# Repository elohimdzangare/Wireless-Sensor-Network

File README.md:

# ESP32 Wireless Sensor Network

A wireless environmental monitoring system using battery powered ESP32 sensor nodes that measure temperature, humidity and light across three locations. A central gateway collects everything and sends it to MATLAB for live plotting and logging.

**Status:** Core system is built and working end to end (nodes to gateway to MATLAB). All three nodes and the gateway have since been redesigned as custom PCBs. Not currently running further test sessions, though one more test run may happen in the future.

---

## Overview

Three sensor nodes (Room A, B, C) each have a DHT22 and a BH1750 sensor and run off 4x AA batteries. Each node wakes up from deep sleep, takes a reading, sends it to the gateway over ESP-NOW, tells the gateway how long it's about to sleep for, then powers down again. The gateway stays on all the time, keeps track of all three nodes, manages 8 status LEDs, and forwards everything to MATLAB over TCP so it can be logged and plotted live.

Rooms are just labelled A, B and C for now instead of actual room names, so the sensors can be moved around without having to change any code. A separate note of what each letter actually corresponds to is kept somewhere.

---

## Possible Applications

- **Greenhouse or shed monitoring**: battery powered nodes with long sleep intervals make sense for outbuildings that don't have easy power access, where you still want to know conditions without running cables.
- **Home climate monitoring**: tracking temperature, humidity and light across different rooms to spot patterns, like which rooms run cold in winter or get too much direct sun, without needing a smart home hub.
- **Damp/mould risk detection**: persistently high humidity in an enclosed space like a basement is an early warning sign for mould risk, this system could flag rooms worth checking on.

---

## Repo Structure

```
/sensor-network
├── README.md
├── sensor_log.txt
├── /gateway
│   └── gateway_matlab.ino       (final gateway sketch)
├── /node
│   └── sensor_node_final.ino    (final sensor node sketch, used on all 3 nodes)
├── /matlab
│   └── src.m
└── /archive                     (earlier test sketches, kept for reference)
    ├── sensor_test.ino
    ├── sensor_node_test.ino
    ├── gateway_receive_test.ino
    ├── gateway_receive_final.ino
    └── hotspot_connection_test.ino
└── /images                     (images of the network)
    ├── Full Network.jpg
    ├── Gateway 3D Render.png
    ├── Gateway PCB Layout.png
    ├── Gateway.jpg 
    ├── Node 3D Render.png
    ├── Node PCB Layout.png 
    ├── Sensor Nodes.jpg
    ├── gateway_schematic.png
    ├── node_schematic.png
    └── updated node schematic.png
```

The `/archive` folder is just earlier versions and one-off test sketches from along the way (testing the sensors before adding ESP-NOW, testing the gateway before connecting it to MATLAB, etc). Not needed to actually run the project, just there to show how it was built up step by step.

---

## Hardware

| Component | Quantity | Notes |
|-----------|----------|-------|
| ESP32 (regular size) | 4 | 3 sensor nodes + 1 gateway |
| DHT22 (AZDelivery) | 3 | Temperature and humidity, one per node |
| BH1750FVI (ARCELI) | 3 | Light level in lux, one per node |
| 4x AA batteries | 3 sets | One set per sensor node, into VIN |
| LEDs | 8 | All status LEDs are on the gateway |
| Resistors | 8 | 470Ω, used for all LEDs regardless of colour |

> **Sensor power:** both sensors on every node need their VCC wired to the ESP32's 3.3V pin, not VIN. VIN is unregulated, so it just passes whatever voltage is feeding it straight through. Wiring a sensor to VIN instead of 3.3V caused issues, more on that in the Debugging section below.

> **Gateway power:** currently running off USB during testing (power bank or laptop). The 5V pin from USB powers the LED circuit. All ESP32 ground pins are tied to a shared ground.

---

## Network Architecture

```
[Node: Room A]  DHT22 + BH1750  ──┐
[Node: Room B]  DHT22 + BH1750  ──┼──(ESP-NOW)──> [Gateway ESP32] ──(TCP, port 8080)──> [MATLAB]
[Node: Room C]  DHT22 + BH1750  ──┘
   4x AA, deep sleep                              connected to WiFi, always on
```

- **Nodes to gateway:** ESP-NOW. Deep sleep wipes the chip's RAM every time it wakes up, so reconnecting to WiFi from scratch each cycle would take 1 to 3 seconds and use a lot of current for a battery powered node. ESP-NOW skips all that, the node just re-registers the gateway as a peer and sends straight away, no router needed.
- **Gateway to MATLAB:** TCP over WiFi. Only the gateway needs an actual WiFi connection since it's the only one that's always awake, so it only pays that startup cost once.
- **WiFi channel:** ESP-NOW and the gateway's WiFi connection use the same radio, so they need to be on the same channel. The nodes default to channel 1 since they never actually connect to WiFi. So far the gateway has landed on channel 1 both times it connected, once to a phone hotspot and once to home WiFi, so this hasn't been an issue yet. If it ever lands on a different channel, ESP-NOW between the nodes and gateway would stop working without much warning.

---

## Sensor Node Behaviour

Every wake cycle goes through `setup()` from scratch, since deep sleep wipes RAM and there's no way to "resume" where you left off:

1. Wake up from deep sleep (timer based)
2. Set up sensors, with a short delay to let them stabilise
3. Set up WiFi station mode and ESP-NOW, re-register the gateway as a peer
4. Read the DHT22 and BH1750
5. Build a `MSG_DATA` packet and send it to the gateway, including flags for whether each sensor read worked
6. Send a `MSG_SLEEP` packet saying how long it's about to sleep for
7. Set the wake up timer and go into deep sleep

Each node currently sleeps for **360 seconds (6 minutes)**, which works out to 10 readings an hour. Each node tells the gateway its own sleep duration in the sleep message, so if you ever want to change one node's interval you don't need to touch the gateway code at all.

> **Sensor settling time:** right after waking up, the sensors need a moment before their first reading can be trusted, especially the DHT22 which often fails its very first read after power up. The node code adds about a 2 second delay before reading, and retries the DHT22 once if the first attempt comes back invalid.

### Data Packet Structure

```cpp
typedef struct {
  uint8_t  node_id;             // 1 = Room A, 2 = Room B, 3 = Room C
  uint8_t  msg_type;            // 0 = MSG_DATA, 1 = MSG_SLEEP
  float    temperature;         // in °C, -999 if DHT22 failed
  float    humidity;            // in %, -999 if DHT22 failed
  float    lux;                 // -999 if BH1750 failed
  bool     dht_ok;
  bool     bh1750_ok;
  uint32_t sleep_duration_sec;  // only matters when msg_type == MSG_SLEEP
} SensorPacket;
```

A node always sends a data packet every cycle, even if a sensor failed. The idea is that whether a node can be reached and whether its sensors are actually working should be tracked separately, so a broken sensor doesn't make the whole node look offline. If a reading fails it just gets sent as -999 with the matching `_ok` flag set to false.

---

## Gateway Behaviour

- Runs a boot sequence with all the LEDs as a quick self test, then connects to WiFi and starts a TCP server on port 8080
- Stays on all the time, accepts a MATLAB connection whenever one comes in
- Handles incoming ESP-NOW packets based on `msg_type`:
  - `MSG_SLEEP` works out when that node should next wake up (current time plus the sleep duration it gave plus a grace window) and turns that node's awake LED off
  - `MSG_DATA` flashes the RX LED, turns the awake LED back on, updates whether that node has a sensor fault, clears any "unreachable" flag, and forwards the data to MATLAB
- Keeps checking if any sleeping node has gone past its expected wake up time, and flags it as unreachable if so
- Sends `STATUS:`, `ERROR:` and `DATA:` messages to Serial and to MATLAB at the same time
- Flashes the TX LED every time something gets sent to MATLAB

---

## Gateway LEDs

| LED | Colour | What it does |
|-----|--------|---------------|
| Room A RX | Blue | Flashes for 100ms when a packet comes in from Room A |
| Room A Awake/Asleep | White | On while Room A is awake, off once it announces it's sleeping |
| Room B RX | Orange | Flashes for 100ms when a packet comes in from Room B |
| Room B Awake/Asleep | White | On while Room B is awake, off once it announces it's sleeping |
| Room C RX | Yellow | Flashes for 100ms when a packet comes in from Room C |
| Room C Awake/Asleep | White | On while Room C is awake, off once it announces it's sleeping |
| Data Sent (TX to MATLAB) | Green | Flashes for 100ms whenever a message goes out to MATLAB |
| Error | Red | See the error states below |

All the LED flashing is non-blocking. The usual way to blink an LED is `digitalWrite(HIGH)`, then `delay(100)`, then `digitalWrite(LOW)`, but `delay()` freezes the whole chip for that time, including the part that listens for incoming ESP-NOW packets. So instead, the gateway just remembers what time an LED turned on, and checks on every loop whether 100ms has passed yet to turn it back off. Same blink, but the gateway never actually stops and can't miss a packet while waiting.

### Error LED States

| State | Behaviour | What it means |
|-------|-----------|----------------|
| `ERROR_NONE` | Off | Everything's fine |
| `ERROR_SENSOR_FAULT` | Slow blink, 500ms on/off | A node is still reachable but one of its sensors failed |
| `ERROR_NODE_UNREACHABLE` | Solid on | A node didn't wake up in time, missed its expected window |

If both are happening at once, unreachable wins and the LED goes solid. The reason behind this is that a node going completely silent is worse than one sensor on one node acting up.

### Gateway Pin Assignments

| Define | GPIO | LED |
|--------|------|-----|
| `A_RX` | 27 | Room A Receive |
| `A_AWAKE` | 14 | Room A Awake |
| `B_RX` | 32 | Room B Receive |
| `B_AWAKE` | 33 | Room B Awake |
| `C_RX` | 4 | Room C Receive |
| `C_AWAKE` | 16 | Room C Awake |
| `HUB_ERROR` | 22 | Error |
| `HUB_RECEIVE` | 19 | Data Sent / TX to MATLAB |

### Node Pin Assignments (same on all 3 nodes)

| Function | GPIO |
|----------|------|
| BH1750 SDA | 26 |
| BH1750 SCL | 27 |
| DHT22 Data | 25 |

### Boot Sequence

When the gateway powers on, it runs through a little self test before doing anything else: every LED pin gets forced LOW first (some GPIO pins can come up HIGH for a moment on boot before any code runs, so this clears that out), then each LED lights up one at a time, then all 8 flash together twice, then everything turns off and normal operation starts.

### LED Resistors

| Colour | Forward Voltage |
|--------|------------------|
| Red | 2.0-2.2V |
| Blue | 3.0-3.2V |
| White | 3.0-3.2V |
| Yellow | 1.8-2.0V |
| Green | 3.0-3.2V |
| Orange | 1.8-2.0V |

All LEDs are rated for 20mA forward current. A single 470Ω resistor value was used for every LED regardless of colour, just for simplicity. This means they're not all running at the same brightness or current, but it's not really an issue since these are just status indicators and don't need to be especially bright.

---

## Message Protocol

All messages are sent line by line from the gateway, to both Serial and to MATLAB over TCP at the same time.

```
STATUS:GATEWAY_READY
STATUS:ROOMA_SLEEPING:duration=360
STATUS:ROOMA_RECONNECTED
ERROR:ROOMB_TIMEOUT
ERROR:ROOMC_DHT_FAILURE
ERROR:ROOMC_BH1750_FAILURE
DATA:ROOMA:24.50,68.90,73.33
```

- `DATA:<ROOM>:<temperature>,<humidity>,<lux>`, one line per node per reading
- `STATUS:<ROOM>_SLEEPING:duration=<seconds>`, sent right before a node powers down
- `STATUS:<ROOM>_RECONNECTED`, sent if a node that had been flagged unreachable sends data again
- `ERROR:<ROOM>_TIMEOUT`, a node missed its expected wake up window
- `ERROR:<ROOM>_DHT_FAILURE` / `ERROR:<ROOM>_BH1750_FAILURE`, sent alongside the data line when a sensor on an otherwise working node fails

---

## Timeout / Error Logic

A fixed timeout doesn't really work once nodes are sleeping for minutes at a time, it would keep falsely triggering during completely normal sleep. So instead:

- When a sleep message comes in, the gateway works out `expected_wake_time = millis() + (sleep_duration_sec * 1000) + GRACE_WINDOW_MS`
- `ERROR:ROOMX_TIMEOUT` only fires if that node hasn't sent a data packet by its own `expected_wake_time`
- Any data packet clears the unreachable flag and resets the expected wake time back to 0 until the next sleep message
- If a node comes back after being flagged unreachable, the gateway sends `STATUS:ROOMX_RECONNECTED`

**Current values:**
- Sleep interval: 360 seconds (6 minutes), 10 readings an hour
- Grace window: 25 seconds, picked to comfortably cover a typical wake up to send cycle (roughly 2-3 seconds: booting, sensor settling, reconnecting WiFi/ESP-NOW, reading, sending) with some buffer for slower cycles, while still being small compared to the 6 minute interval

---

## MATLAB Responsibilities

- Connects to the gateway with `tcpclient(GATEWAY_IP, 8080)`
- Reads incoming lines and checks the prefix:
  - `STATUS:` gets printed to console with a timestamp and written to the log file
  - `ERROR:` gets printed to console (in red, via stderr) and written to the log file
  - `DATA:` gets parsed into temperature/humidity/lux per room and the live plots get updated
- Logs every `STATUS`/`ERROR` message into `sensor_log.txt`, which keeps appending across sessions
- Plots live data in 3 stacked subplots (temperature, humidity, light), each one showing all 3 rooms as separate lines, with a rolling window of recent points

> The gateway's IP address can change depending on whatever network it joins, since it's assigned by DHCP. The Serial Monitor must be checked each session and update the IP in the MATLAB script if needed.

---

## Debugging / Errors Encountered

A running list of the actual problems hit while building this, since most of them weren't obvious from the code alone.

**LED wouldn't light up no matter what**
Spent ages checking polarity, resistor values, GPIO pin mapping, even swapped pins entirely. Eventually traced it to the breadboard itself. The long breadboard I had purchased had a physical gap splitting the ground rail into two separate halves that aren't actually connected to each other. The ESP32's ground was in one half and the LED circuit's ground was in the other half, so they were never connected despite looking like the same rail. Fixed by bridging both halves with a jumper wire.

**BH1750 "device not configured" error, but only sometimes**
The BH1750 worked fine on a direct 6V supply but kept failing with this error once running off USB. Turned out both sensors had their VCC wired to VIN instead of 3.3V. VIN is unregulated so it just passes through whatever is feeding it, meaning the BH1750 (rated for 2.4 to 3.6V) was actually running at close to 5 or 6V depending on the power source. It happened to behave at 6V but not at 5V from USB, which made it look inconsistent rather than just wrong. Moving both sensors' VCC to the 3.3V pin fixed it completely. This also matters for the battery powered nodes specifically, since a sensor wired to VIN would get less reliable as the battery drains.

**GPIO14 turning on by itself before any code ran**
Powered on the gateway and noticed one LED was already lit before any sketch had even done anything. Some ESP32 GPIO pins default to a HIGH state for a moment during boot, before `setup()` runs. Fixed by forcing every LED pin LOW right at the very start of the boot sequence function.

**Error LED stuck blinking even while a node was asleep**
After adding deep sleep, the gateway kept showing a sensor fault for a node that was just sleeping normally. This was because the gateway didn't yet know how to tell apart a sleep announcement from a regular data packet, so the last reading it saw before the node went quiet (which happened to have a sensor fault from sensors not being settled yet) just stayed stuck. Fixed by adding sensor settling delays on the node side, and by having the gateway properly handle `MSG_SLEEP` messages separately from `MSG_DATA`.

---

## Future Features (Not Built Yet)

- **Remote reset for all nodes:** thought about having the gateway broadcast a reset command over ESP-NOW, but since nodes are asleep most of the time and ESP-NOW only reaches devices that are actually awake, this wouldn't reliably reset a sleeping node. Still trying to figure out a good solution for this that works with the nodes being in separate rooms.
- **Rebuilding a day's data from the log file:** a MATLAB script that could take `sensor_log.txt` and reconstruct/replay what happened on any given day, instead of only being able to see things live.
-  **Small LED screen on the gateway:** an idea to add a small display (like an OLED or LCD) to the gateway that prints the same messages currently going to Serial Monitor. Would mean you could see status/error messages without needing a laptop plugged in and Arduino IDE open, which would be useful once the gateway is meant to just run on its own.

---

## Confirmed Working

- ESP-NOW and the gateway's WiFi connection working together on channel 1, tested with both a phone hotspot and home WiFi
- All 3 nodes sending data and sleep announcements correctly
- Gateway correctly telling apart sensor faults from unreachable nodes, with the right LED priority
- Full pipeline working end to end: node, ESP-NOW, gateway, TCP, MATLAB, including live plotting and logging

---

## Test Results

### Test 1, 23 June 2026 (~7.5 hours)

Room mapping for this test:
- Room A: Backyard
- Room B: Basement
- Room C: Bedroom

No artificial lighting was used in any room during this test.

No timeouts or sensor faults occurred during this run. Full log available [here](sensor_log.txt), room labels [here](tests/test1-23.06.26/room_labels.txt).

The basement (Room B) stayed noticeably more stable in both temperature and humidity than the other two rooms, which makes sense given it's underground and shielded from outdoor temperature swings. The light readings line up well with expected sun position and window placement throughout the afternoon and evening, with the bedroom (Room C) starting brightest from direct sun and dropping off sharply once the sun moved off that window, while the backyard (Room A) decayed more gradually as expected outdoors.

---

## PCB Version

Both the sensor nodes and the gateway have since been redesigned as custom PCBs in KiCad.

**Node:** Same circuit as the breadboard version (ESP32 DevKitC, DHT22, BH1750), with the addition of a 2-pin battery connector (J1) wired directly to the ESP32's 5V and GND pins, so each node can be powered by a battery through the PCB itself.

**Gateway:** No schematic changes, only a new PCB layout. The gateway continues to run off the ESP32's USB-C power, same as the breadboard version.

<p align="center">
  
  <br/>
  <em>Figure 1: Updated Node Schematic</em>
</p>

<br/>

<p align="center">
  
  <br/>
  <em>Figure 2: Node PCB Layout</em>
</p>

<br/>

<p align="center">
  
  <br/>
  <em>Figure 3: Node PCB 3D Render</em>
</p>

<br/>

<p align="center">
  
  <br/>
  <em>Figure 4: Gateway PCB Layout</em>
</p>

<br/>

<p align="center">
  
  <br/>
  <em>Figure 5: Gateway PCB 3D Render</em>
</p>

KiCad project files: [WSN KiCad Files](WSN%20KiCad%20Files)

---

## Build Order (roughly how it actually went)

1. Sensor node firmware: reading sensors, then ESP-NOW transmission
2. Gateway firmware: ESP-NOW receiving, LEDs (RX, then error/fault states, then awake/asleep), boot sequence
3. Deep sleep and sleep announcements on the nodes, expected wake window timeout logic on the gateway
4. Gateway WiFi connection and channel check
5. Gateway TCP server and the message protocol
6. MATLAB script: connecting, parsing, logging, live plotting

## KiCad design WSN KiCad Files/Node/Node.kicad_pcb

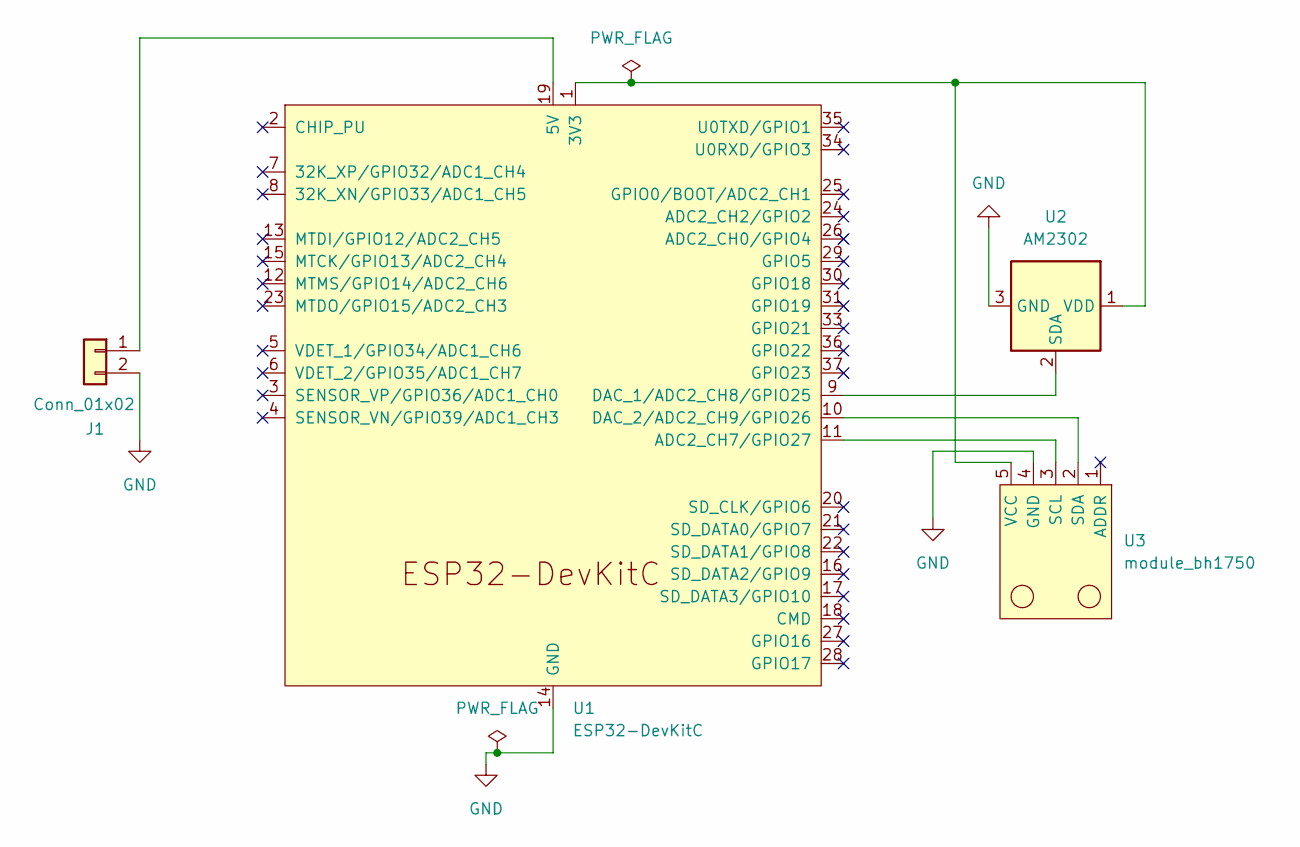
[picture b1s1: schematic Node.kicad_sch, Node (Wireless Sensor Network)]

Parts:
J1: Conn_01x02; PinHeader_1x02_P2.00mm_Vertical
U1: ESP32-DevKitC
U2: AM2302; ASAIR_AM2302_P2.54mm_Vertical
U3: module_bh1750

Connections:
GND: J1.2, U1.14 (GND), U1.32 (GND), U1.38 (GND), U2.3 (GND), U2.4 (GND), U3.4 (GND)
unnamed: J1.1, U1.19 (5V)
unnamed: U1.1 (3V3), U2.1 (VDD), U3.5 (VCC)
unnamed: U1.11 (ADC2_CH7/GPIO27), U3.3 (SCL)
unnamed: U1.9 (DAC_1/ADC2_CH8/GPIO25), U2.2 (SDA)
unnamed: U1.10 (DAC_2/ADC2_CH9/GPIO26), U3.2 (SDA)

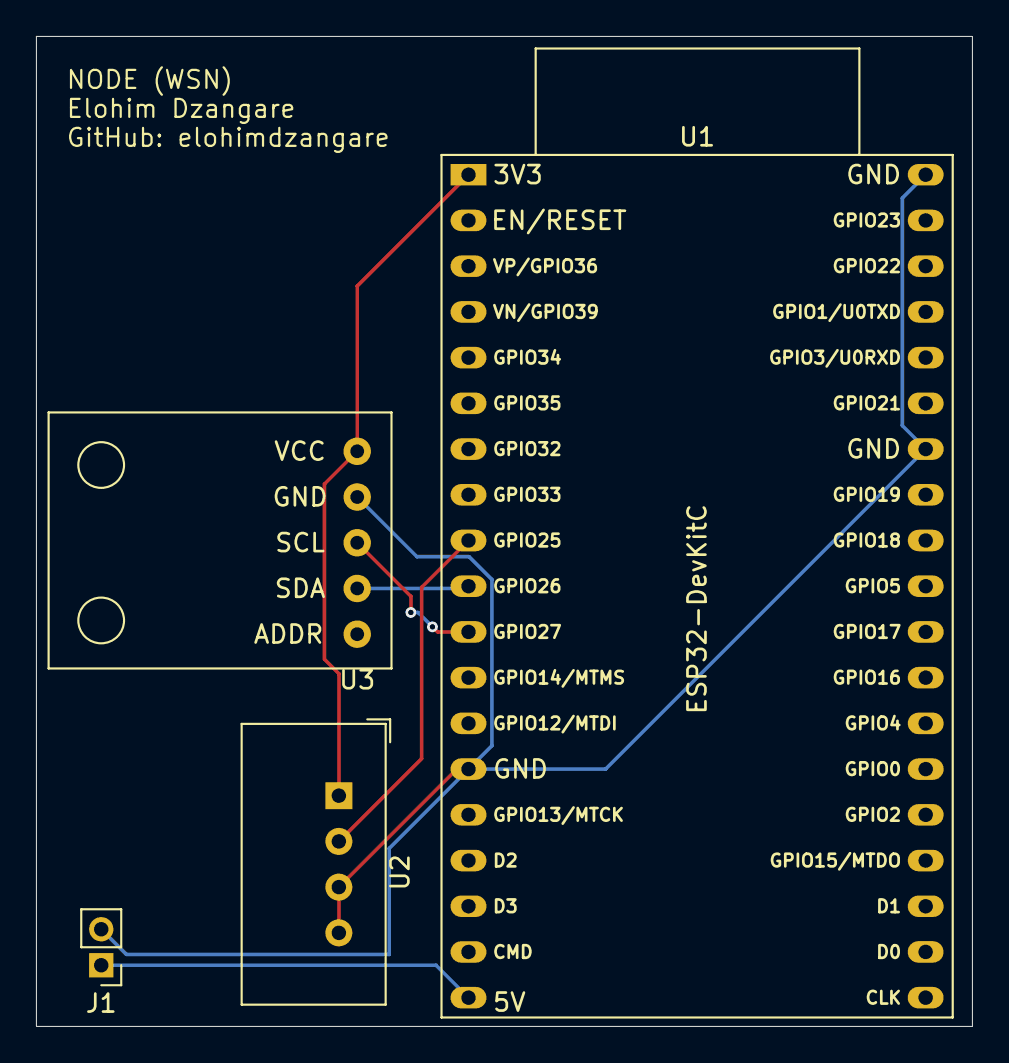
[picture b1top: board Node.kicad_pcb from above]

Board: 2 copper layers, 52.0 x 55.0 mm, 4 parts (0 on the bottom side), 6 nets.

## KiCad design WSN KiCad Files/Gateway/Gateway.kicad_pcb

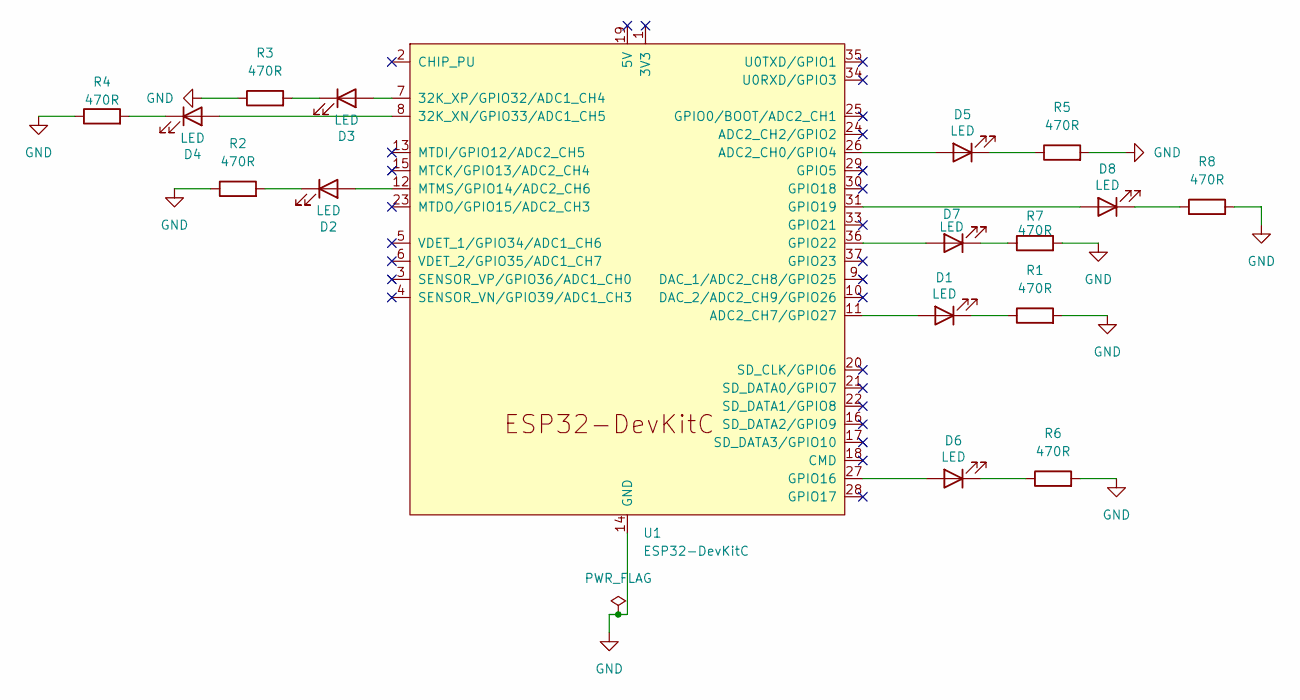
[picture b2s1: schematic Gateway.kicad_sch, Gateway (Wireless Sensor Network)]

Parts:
D1, D2, D3, D4, D5, D6, D8: LED; LED_D5.0mm_Clear
D7: LED; LED_D5.0mm
R1, R2, R3, R4, R5, R6, R7, R8: 470R; R_Axial_DIN0204_L3.6mm_D1.6mm_P7.62mm_Horizontal
U1: ESP32-DevKitC

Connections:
GND: R1.2, R2.1, R3.1, R4.1, R5.2, R6.2, R7.2, R8.2, U1.14 (GND), U1.32 (GND), U1.38 (GND)
unnamed: D1.2 (A), U1.11 (ADC2_CH7/GPIO27)
unnamed: D1.1 (K), R1.1
unnamed: D2.2 (A), U1.12 (MTMS/GPIO14/ADC2_CH6)
unnamed: D2.1 (K), R2.2
unnamed: D3.2 (A), U1.7 (32K_XP/GPIO32/ADC1_CH4)
unnamed: D3.1 (K), R3.2
unnamed: D4.2 (A), U1.8 (32K_XN/GPIO33/ADC1_CH5)
unnamed: D4.1 (K), R4.2
unnamed: D5.2 (A), U1.26 (ADC2_CH0/GPIO4)
unnamed: D5.1 (K), R5.1
unnamed: D6.2 (A), U1.27 (GPIO16)
unnamed: D6.1 (K), R6.1
unnamed: D7.2 (A), U1.36 (GPIO22)
unnamed: D7.1 (K), R7.1
unnamed: D8.2 (A), U1.31 (GPIO19)
unnamed: D8.1 (K), R8.1

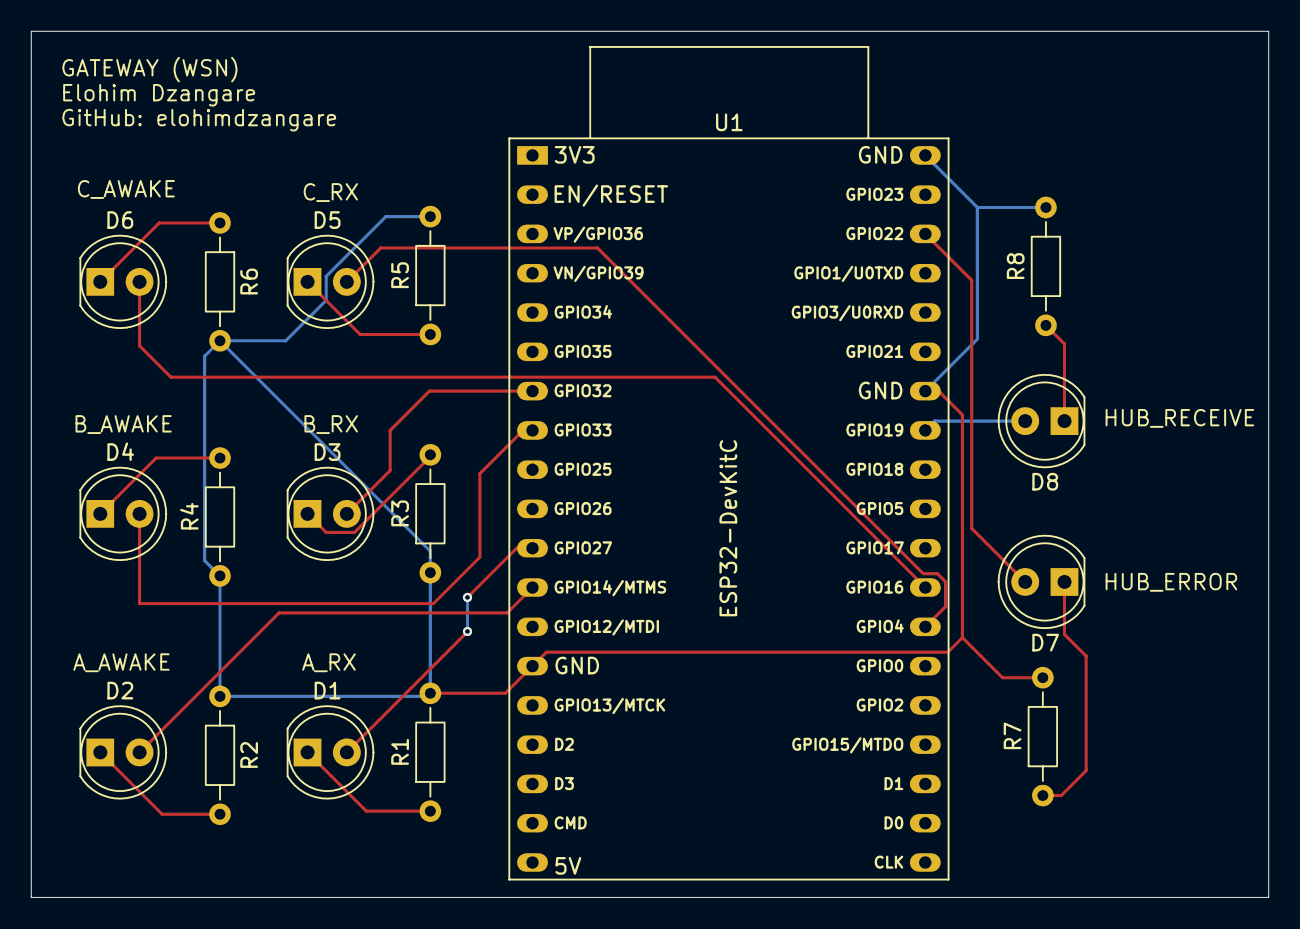
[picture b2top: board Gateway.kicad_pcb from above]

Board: 2 copper layers, 80.0 x 56.0 mm, 17 parts (0 on the bottom side), 17 nets.

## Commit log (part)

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2026-06-23 Add files
2026-06-23 update files
2026-06-23 add test1 files
